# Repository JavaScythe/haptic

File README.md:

# haptic
8 channel 2A motor with flyback protection USB controller with 5 extra exposed GPIOs

Why? To take advantage of the low pricing of these motors, while driving them in a cost efficient but low latency and sufficiently powered manner.

### BOM
|Name          |Quantity|Price Total  |Link  |
|--------|-------|--------|------|
|RK-370|8|24.37|aliexpress.us/item/3256806031375057.html|
|PCBA|2 (minimum)|25.09|JLCPCB, see gerbers|

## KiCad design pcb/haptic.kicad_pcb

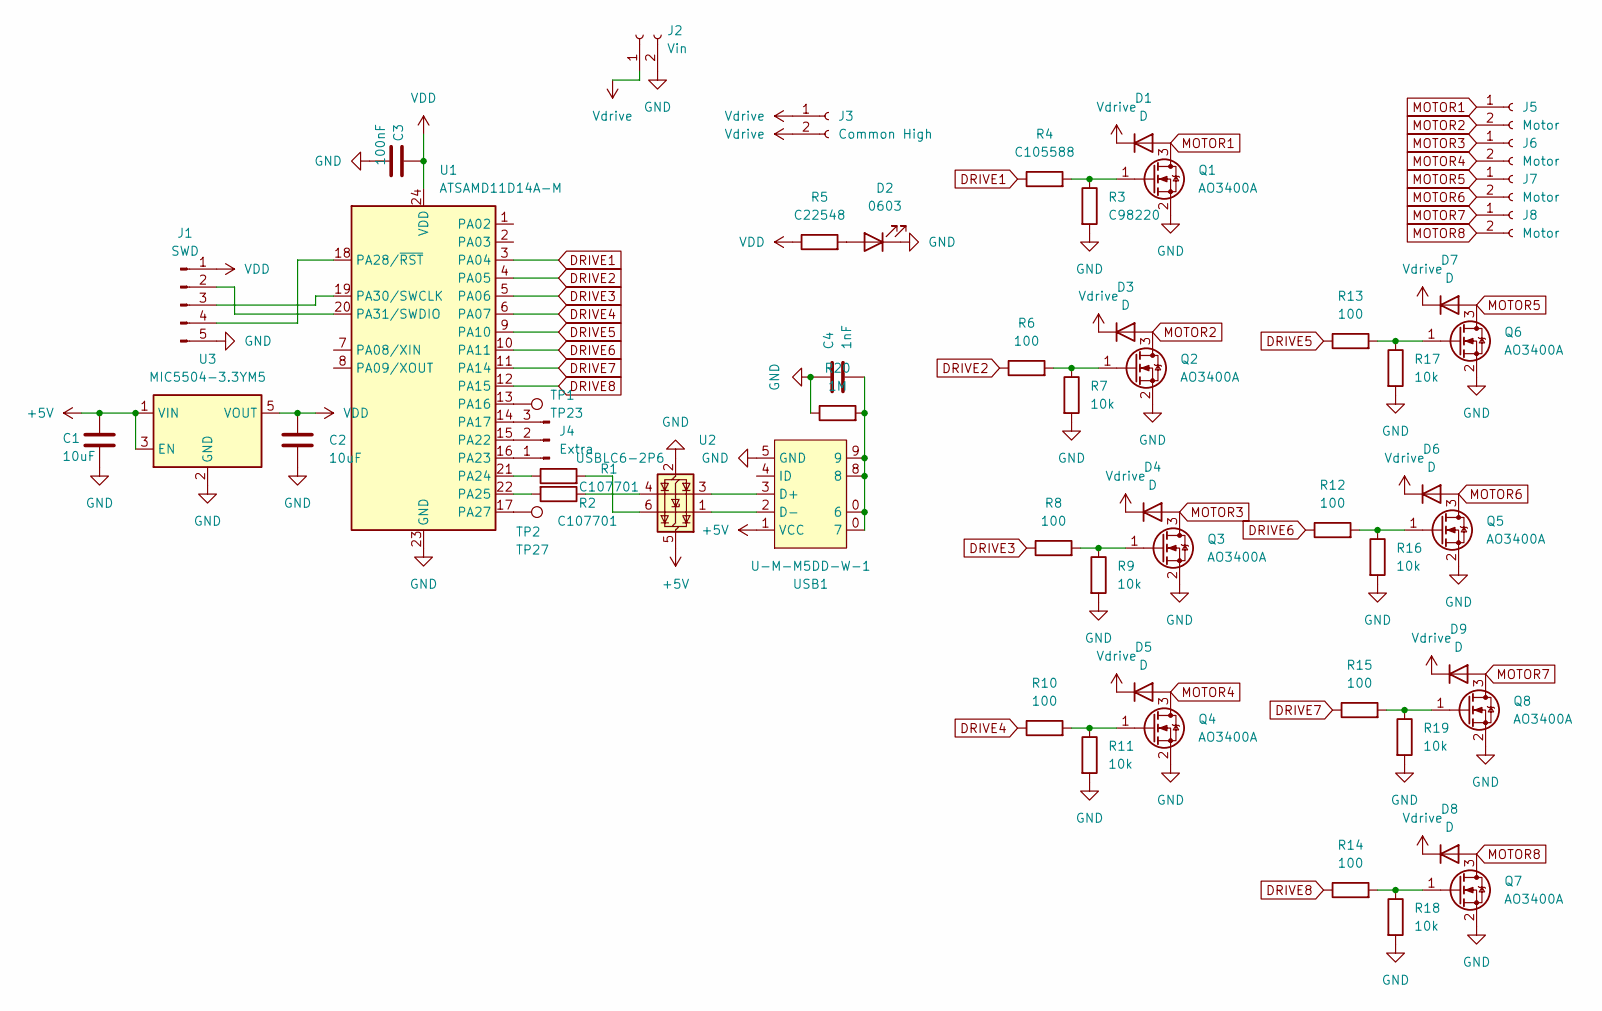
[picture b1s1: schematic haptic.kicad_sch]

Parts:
C1, C2: 10uF; C_0603_1608Metric
C3: 100nF; C_0603_1608Metric
C4: 1nF; C_0603_1608Metric
D1, D3, D4, D5, D6, D7, D8, D9: D; D_SOD-123
D2: 0603; LED_0603_1608Metric
J1: SWD; PinHeader_1x05_P2.54mm_Vertical
J2: Vin; CONN-TH_DB301V-3.5-2P-GN
J3: Common High; CONN-TH_DB301V-3.5-2P-GN
J4: Extra; PinHeader_1x03_P2.54mm_Vertical
J5, J6, J7, J8: Motor; CONN-TH_DB301V-3.5-2P-GN
Q1, Q2, Q3, Q4, Q5, Q6, Q7, Q8: AO3400A; SOT-23
R1, R2: C107701; R_0603_1608Metric
R3: C98220; R_0603_1608Metric
R4: C105588; R_0603_1608Metric
R5: C22548; R_0603_1608Metric
R6, R8, R10, R12, R13, R14, R15: 100; R_0603_1608Metric
R7, R9, R11, R16, R17, R18, R19: 10k; R_0603_1608Metric
R20: 1M; R_0603_1608Metric
TP1: TP23; TestPoint_Pad_1.0x1.0mm
TP2: TP27; TestPoint_Pad_1.0x1.0mm
U1: ATSAMD11D14A-M; QFN-24-1EP_4x4mm_P0.5mm_EP2.6x2.6mm
U2: USBLC6-2P6; SOT-666
U3: MIC5504-3.3YM5; SOT-23-5
USB1: U-M-M5DD-W-1; USB-MINI-SMD_U-M-M5DD-W-1; LCSC Part C145778

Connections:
+5V: C1.1, U2.5 (VBUS), U3.1 (VIN), U3.3 (EN), USB1.1 (VCC)
DRIVE1: R4.1, U1.3 (PA04)
DRIVE2: R6.1, U1.4 (PA05)
DRIVE3: R8.1, U1.5 (PA06)
DRIVE4: R10.1, U1.6 (PA07)
DRIVE5: R13.1, U1.9 (PA10)
DRIVE6: R12.1, U1.10 (PA11)
DRIVE7: R15.1, U1.11 (PA14)
DRIVE8: R14.1, U1.12 (PA15)
GND: C1.2, C2.2, C3.2, C4.1, D2.1 (K), J1.5, J2.2, Q1.2 (S), Q2.2 (S), Q3.2 (S), Q4.2 (S), Q5.2 (S), Q6.2 (S), Q7.2 (S), Q8.2 (S), R3.2, R7.2, R9.2, R11.2, R16.2, R17.2, R18.2, R19.2, R20.1, U1.23 (GND), U2.2 (GND), U3.2 (GND), USB1.5 (GND)
MOTOR1: D1.2 (A), J5.1, Q1.3 (D)
MOTOR2: D3.2 (A), J5.2, Q2.3 (D)
MOTOR3: D4.2 (A), J6.1, Q3.3 (D)
MOTOR4: D5.2 (A), J6.2, Q4.3 (D)
MOTOR5: D7.2 (A), J7.1, Q6.3 (D)
MOTOR6: D6.2 (A), J7.2, Q5.3 (D)
MOTOR7: D9.2 (A), J8.1, Q8.3 (D)
MOTOR8: D8.2 (A), J8.2, Q7.3 (D)
unnamed: D2.2 (A), R5.2
unnamed: J1.2, U1.20 (PA31/SWDIO)
unnamed: J1.3, U1.19 (PA30/SWCLK)
unnamed: J1.4, U1.18 (PA28/~RST)
unnamed: J4.1, U1.16 (PA23)
unnamed: J4.2, U1.15 (PA22)
unnamed: J4.3, U1.14 (PA17)
unnamed: Q1.1 (G), R3.1, R4.2
unnamed: Q2.1 (G), R6.2, R7.1
unnamed: Q3.1 (G), R8.2, R9.1
unnamed: Q4.1 (G), R10.2, R11.1
unnamed: Q5.1 (G), R12.2, R16.1
unnamed: Q6.1 (G), R13.2, R17.1
unnamed: Q7.1 (G), R14.2, R18.1
unnamed: Q8.1 (G), R15.2, R19.1
unnamed: R1.2, U2.6 (I/O1)
unnamed: R2.1, U2.4 (I/O2)
unnamed: TP1.1, U1.13 (PA16)
unnamed: R1.1, U1.21 (PA24)
unnamed: R2.2, U1.22 (PA25)
unnamed: TP2.1, U1.17 (PA27)
unnamed: C4.2, R20.2, USB1.0 (7), USB1.8, USB1.9
unnamed: U2.3 (I/O2), USB1.3 (D+)
unnamed: U2.1 (I/O1), USB1.2 (D-)
VDD: C2.1, C3.1, J1.1, R5.1, U1.24 (VDD), U3.5 (VOUT)
Vdrive: D1.1 (K), D3.1 (K), D4.1 (K), D5.1 (K), D6.1 (K), D7.1 (K), D8.1 (K), D9.1 (K), J2.1, J3.1, J3.2

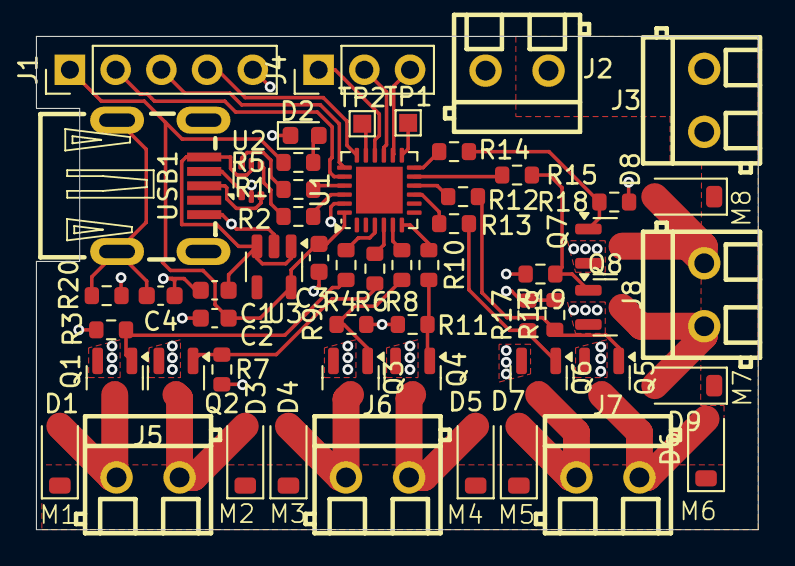
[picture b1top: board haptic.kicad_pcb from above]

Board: 2 copper layers, 40.1 x 27.4 mm, 55 parts (0 on the bottom side), 44 nets.

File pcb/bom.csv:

Designator,Footprint,Quantity,Value,LCSC Part #
"C1, C2",0603,2,10uF,
C3,0603,1,100nF,
C4,0603,1,1nF,
"D1, D3, D4, D5, D6, D7, D8, D9",D_SOD-123,8,D,
D2,0603,1,0603,
J1,PinHeader_1x05_P2.54mm_Vertical,1,SWD,
J2,CONN-TH_DB301V-3.5-2P-GN,1,Vin,
J3,CONN-TH_DB301V-3.5-2P-GN,1,Common High,
J4,PinHeader_1x03_P2.54mm_Vertical,1,Extra,
"J5, J6, J7, J8",CONN-TH_DB301V-3.5-2P-GN,4,Motor,
"Q1, Q2, Q3, Q4, Q5, Q6, Q7, Q8",SOT-23,8,AO3400A,
"R1, R2",0603,2,C107701,
"R10, R12, R13, R14, R15, R6, R8",0603,7,100,
"R11, R16, R17, R18, R19, R7, R9",0603,7,10k,
R20,0603,1,1M,
R3,0603,1,C98220,
R4,0603,1,C105588,
R5,0603,1,C22548,
TP1,TestPoint_Pad_1.0x1.0mm,1,TP23,
TP2,TestPoint_Pad_1.0x1.0mm,1,TP27,
U1,QFN-24-1EP_4x4mm_P0.5mm_EP2.6x2.6mm,1,ATSAMD11D14A-M,
U2,SOT-666,1,USBLC6-2P6,
U3,SOT-23-5,1,MIC5504-3.3YM5,
USB1,USB-MINI-SMD_U-M-M5DD-W-1,1,U-M-M5DD-W-1,C145778

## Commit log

2025-06-24 Create root
